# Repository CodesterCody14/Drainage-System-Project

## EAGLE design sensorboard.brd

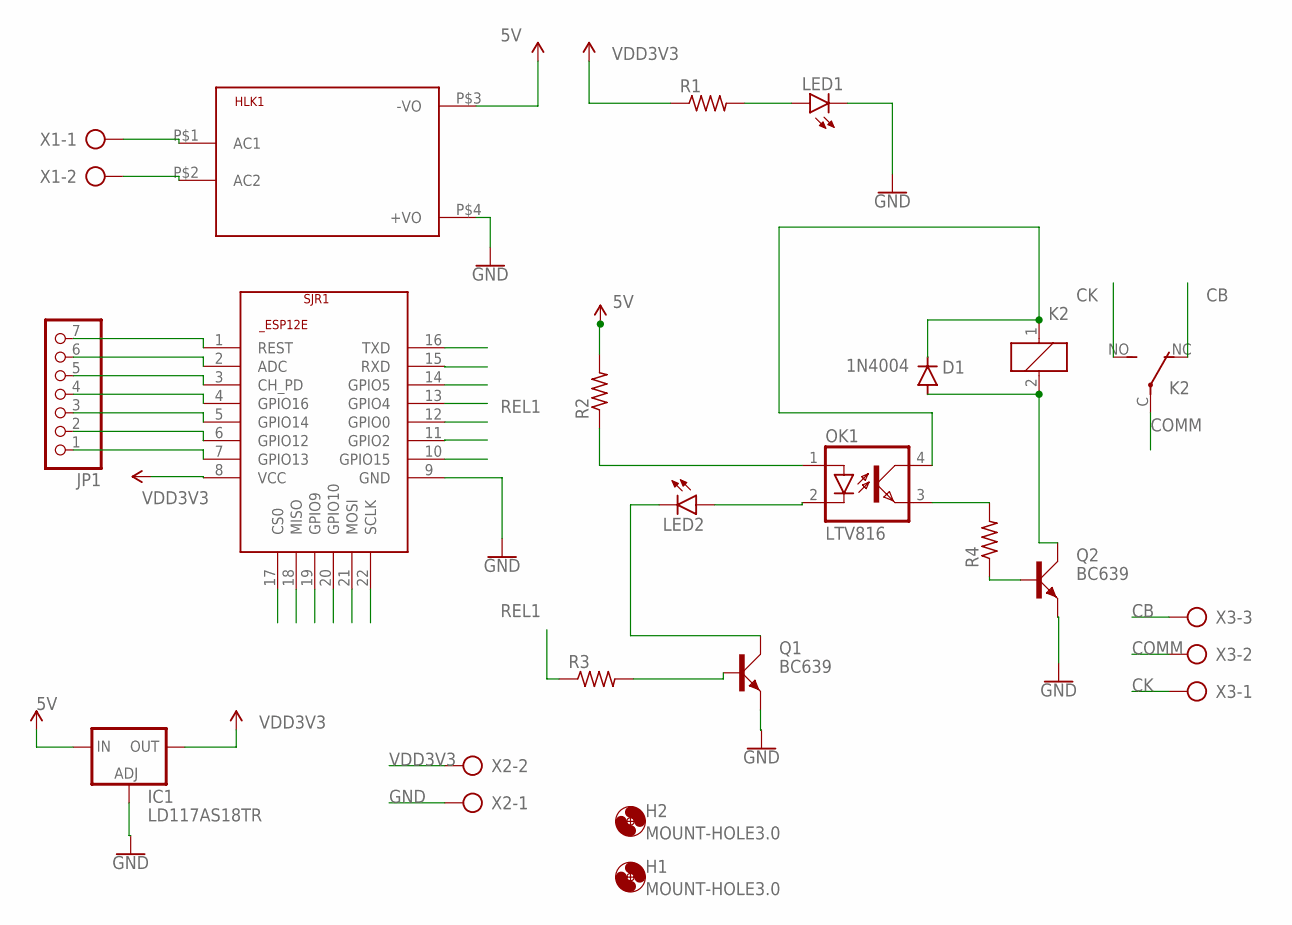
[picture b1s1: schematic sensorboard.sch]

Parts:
D1: 1N4004; DO41-10
H1, H2: MOUNT-HOLE3.0; 3,0
HLK1: HLK-PM013W 5V; HLK-PM01
IC1: LD117AS18TR; SOT223
JP1: PINHD-1X7; 1X07
K2: JTN-PCB-DC18V; JT-PCB
LED1, LED2: LED5MM
OK1: LTV816; DIL04
Q1, Q2: BC639; SOT54D
R1, R2, R3, R4: R-US_0207/5V; 0207/5V
SJR1: ESP8266-12EESP12E; ESP8266-ESP12E
X1, X2: AK500/2
X3: AK500/3

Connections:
5V: HLK1.P$3 (-VO), IC1.3 (IN), R2.2
ADC: JP1.6, SJR1.2 (ADC)
CB: K2.NC (O), X3.3
CH_PD: JP1.5, SJR1.3 (CH_PD)
CK: K2.NO (S), X3.1
COMM: K2.C, X3.2
CSO: SJR1.17 (CS0)
GND: HLK1.P$4 (+VO), IC1.1 (ADJ), LED1.K (C), Q1.E, Q2.E, SJR1.9 (GND), X2.1
GPIO2: SJR1.11 (GPIO2)
GPIO4: SJR1.13 (GPIO4)
GPIO5: SJR1.14 (GPIO5)
GPIO9: SJR1.19 (GPIO9)
GPIO10: SJR1.20 (GPIO10)
GPIO12: JP1.2, SJR1.6 (GPIO12)
GPIO13: JP1.1, SJR1.7 (GPIO13)
GPIO14: JP1.3, SJR1.5 (GPIO14)
GPIO15: SJR1.10 (GPIO15)
GPIO16: JP1.4, SJR1.4 (GPIO16)
MISO: SJR1.18 (MISO)
MOSI: SJR1.21 (MOSI)
unnamed: HLK1.P$1 (AC1), X1.1
unnamed: HLK1.P$2 (AC2), X1.2
unnamed: LED1.A, R1.2
unnamed: OK1.1 (A), R2.1
unnamed: LED2.A, OK1.2 (C)
unnamed: LED2.K (C), Q1.C
unnamed: Q1.B, R3.2
unnamed: OK1.3 (EMIT), R4.2
unnamed: Q2.B, R4.1
unnamed: D1.C, K2.1, OK1.4 (COL)
unnamed: D1.A, K2.2, Q2.C
NRST: JP1.7, SJR1.1 (REST)
REL1: R3.1, SJR1.12 (GPIO0)
RXD0: SJR1.15 (RXD)
SCLK: SJR1.22 (SCLK)
TXDO: SJR1.16 (TXD)
VDD3V3: IC1.4 (OUT), R1.1, SJR1.8 (VCC), X2.2

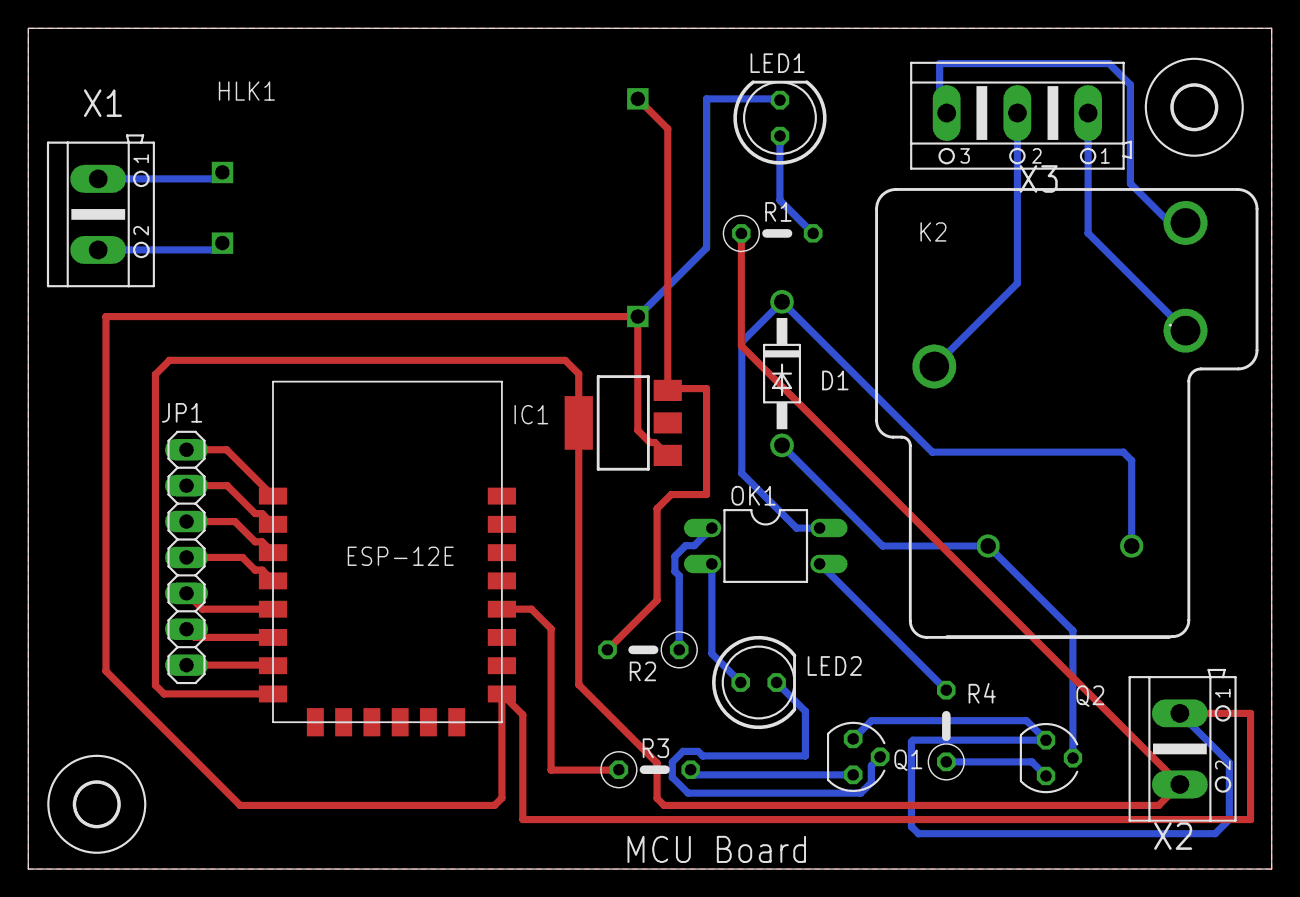
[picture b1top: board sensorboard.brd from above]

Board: 2 copper layers, 88.0 x 59.5 mm, 20 parts (0 on the bottom side), 25 nets.

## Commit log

2021-06-21 Create PCB designing
2021-06-21 Add files via upload
    Version1 (95.50 X 64)mm
2021-06-21 Add files via upload
    Version2 (88 X 59.50)

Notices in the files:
parts and their libraries:
SparkFun-PowerSymbols: Licensing: Creative Commons ShareAlike 4.0 International - https://creativecommons.org/licenses/by-sa/4.0
